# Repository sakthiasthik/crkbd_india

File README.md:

# Corne Indian ⌨️

A split mechanical keyboard **inspired by the original [CRKBD (Corne)](https://github.com/foostan/crkbd)** by [foostan](https://github.com/foostan). While the overall keyboard layout, key positions, and form factor follow the Corne design, the **entire schematic and PCB layout have been redesigned from scratch**.

The hardware has been engineered with a focus on the **Indian maker ecosystem**, using components that are readily available from Indian suppliers. The PCB has been designed to simplify manufacturing, assembly, troubleshooting, and long-term maintenance. If a component fails, it can be replaced easily without requiring hard-to-source imported parts — making the keyboard highly repairable and practical for everyday use.

---

## Highlights

- **Inspired by the CRKBD (Corne) split keyboard design**
- **Complete schematic designed from scratch**
- **Complete PCB layout designed from scratch**
- **Powered by RP2040** — affordable, powerful, and widely available in India (replaces the Pro Micro / ATmega32U4)
- **Hot-swappable switches** — no soldering required for switches
- Optimized for components that are **easily available from Indian suppliers**
- Designed for **easy manufacturing and assembly**
- Simplified **rework and repair** with accessible component placement
- **Fully open-source hardware** — anyone can build, modify, and maintain

---

## Design Files

All design files are in [`pcbs/corne-indian/`](pcbs/corne-indian/):

```
pcbs/corne-indian/corne-inidan-hotswap/
├── corne-inidan-hotswap.kicad_pro    # KiCad project
├── corne-inidan-hotswap.kicad_sch    # Main schematic
├── corne-inidan-hotswap.kicad_pcb    # PCB layout
├── left.kicad_sch                    # Left half schematic
├── right.kicad_sch                   # Right half schematic
├── corne-inidan-hotswap.step         # 3D model
└── corne_ibom.html                   # Interactive BOM
```

> Designed in **KiCad**. Open the `.kicad_pro` file to get started.

---

## Images

### Original CRKBD (Corne) — The Inspiration

### Corne Indian — Our Design

<!-- TODO: Add Corne Indian PCB render (top view) -->

<!-- TODO: Add Corne Indian PCB render (bottom view) -->

<!-- TODO: Add assembled Corne Indian keyboard photo -->

<!-- TODO: Add Corne Indian 3D render -->
<!-- [Corne Indian 3D Render](https://via.placeholder.com/800x600/0f3460/e0e0e0?text=Corne+Indian+-+3D+Render) -->

---

## Comparison: Original CRKBD vs Corne Indian

| Feature | Original CRKBD | Corne Indian |
|---|---|---|
| **Microcontroller** | Pro Micro (ATmega32U4) | RP2040 |
| **Switch mounting** | Soldered / Hotswap | Hot-swappable |
| **Component sourcing** | International | India-focused |
| **Schematic** | Original by foostan | Redesigned from scratch |
| **PCB Layout** | Original by foostan | Redesigned from scratch |
| **License** | MIT | MIT |

---

## Credits

This project stands on the shoulders of the excellent **[CRKBD (Corne)](https://github.com/foostan/crkbd)** by **foostan**. The Corne Indian retains the same split-keyboard layout and form factor that makes the Corne great, while re-engineering the hardware for the Indian maker community.

---

## License

This project is licensed under the **MIT License** — see [LICENSE](LICENSE) for details.

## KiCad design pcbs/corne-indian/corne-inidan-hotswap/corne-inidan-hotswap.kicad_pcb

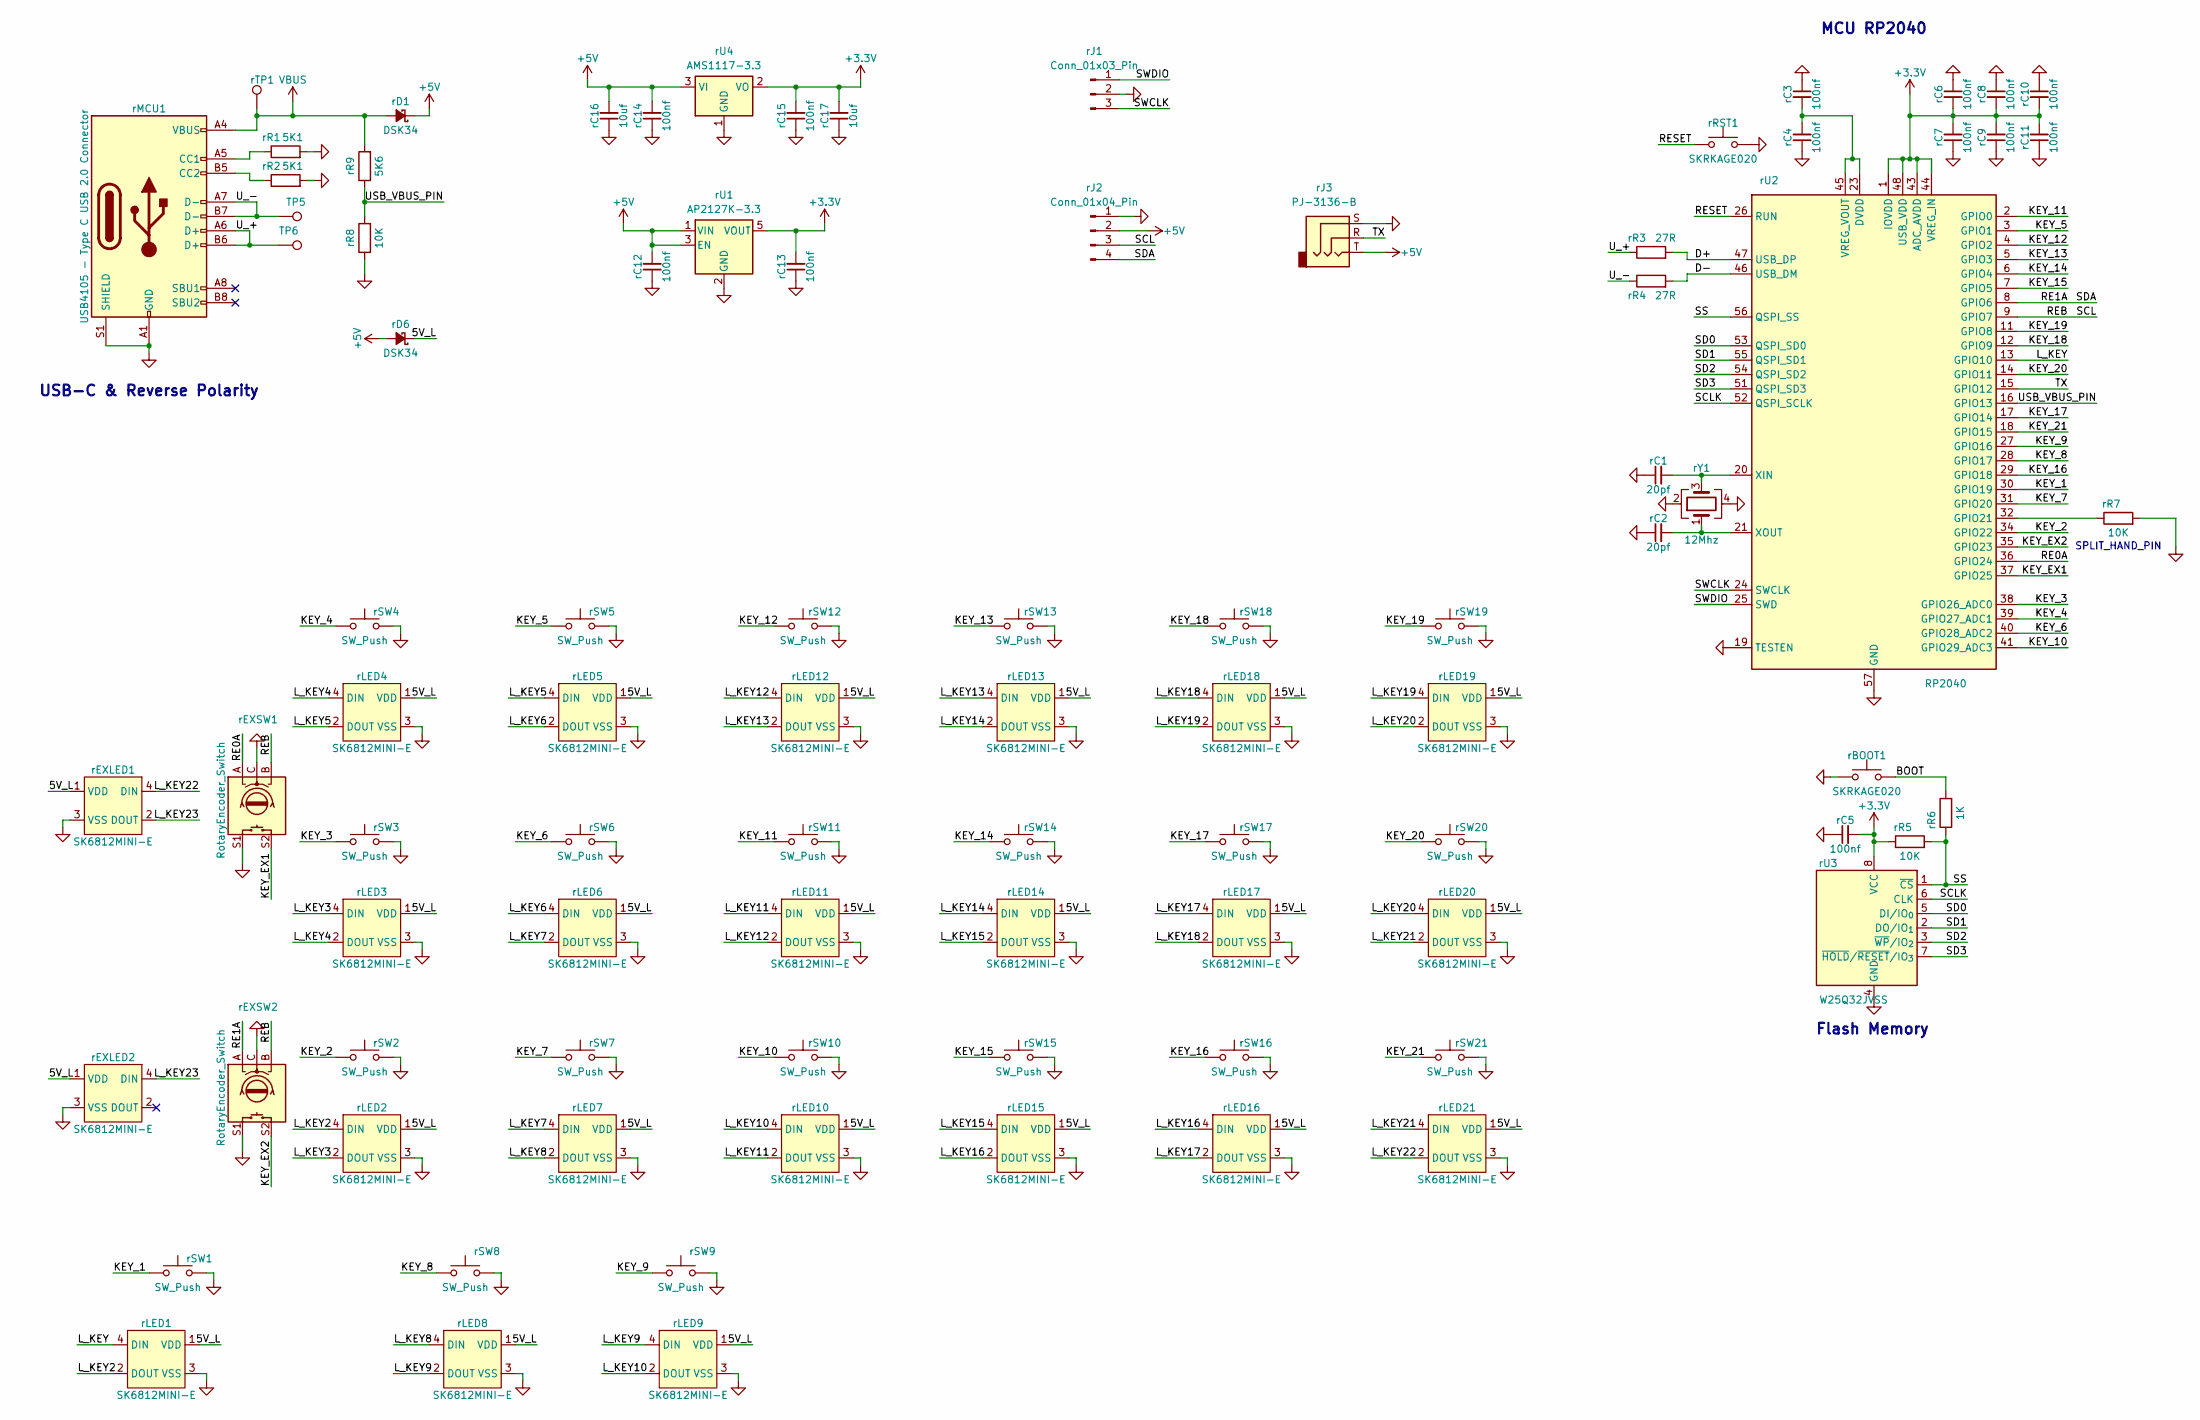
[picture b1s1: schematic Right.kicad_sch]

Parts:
TP5, TP6: TestPoint; TestPoint_Pad_D1.0mm
rBOOT1: SKRKAGE020; SW_Push_SPST_NO_Alps_SKRK; Manufacturer_Part_Number SKRKAGE020; LCSC_Part C18077675
rC1, rC2: 20pf; C_0603_1608Metric
rC3, rC4, rC5, rC6, rC7, rC8, rC9, rC10, rC11, rC12, rC13, rC14, rC15: 100nf; C_0603_1608Metric; Manufacturer_Part_Number MC0603B104K250CT; LCSC_Part C14663
rC16, rC17: 10uf; C_0603_1608Metric
rD1, rD6: DSK34; D_SOD-123F; Manufacturer_Part_Numbe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 DSK34; LCSC_Part C727076
rEXLED1, rEXLED2: SK6812MINI-E; YS-SK6812MINI-E
rEXSW1, rEXSW2: RotaryEncoder_Switch; keyswitch_cherrymx_hotswap_1u_rotary_encoder_ec12
rJ1: Conn_01x03_Pin; PinHeader_1x03_P2.54mm_Vertical
rJ2: Conn_01x04_Pin; PinHeader_1x04_P2.54mm_Vertical
rJ3: PJ-3136-B
rLED1, rLED2, rLED3, rLED4, rLED5, rLED6, rLED7, rLED8, rLED9, rLED10, rLED11, rLED12, rLED13, rLED14, rLED15, rLED16, rLED17, rLED18, rLED19, rLED20, rLED21: SK6812MINI-E; YS-SK6812MINI-E
rMCU1: USB4105 - Type C USB 2.0 Connector; USB_C_Receptacle_GCT_USB4105-xx-A_16P_TopMnt_Horizontal; Manufacturer_Part_Number USB4105-15-A-120; LCSC_Part C2988369
rR1, rR2: 5K1; R_0603_1608Metric; Manufacturer_Part_Number MCWR06X5101FTL; LCSC_Part C23186
rR3, rR4: 27R; R_0603_1608Metric
rR5, rR7, rR8: 10K; R_0603_1608Metric; Manufacturer_Part_Number MCWR06X1002FTL; LCSC_Part C25804
rR6: 1K; R_0603_1608Metric
rR9: 5K6; R_0603_1608Metric
rRST1: SKRKAGE020; SW_Push_SPST_NO_Alps_SKRK; Manufacturer_Part_Number SKRKAGE020; LCSC_Part C18077675
rSW1: SW_Push; SW_Cherry_MX_1.50u_Hotswap
rSW2, rSW3, rSW4, rSW5, rSW6, rSW7, rSW8, rSW9, rSW10, rSW11, rSW12, rSW13, rSW14, rSW15, rSW16, rSW17, rSW18, rSW19, rSW20, rSW21: SW_Push; SW_Cherry_MX_1.00u_Hotswap
rTP1: TestPoint; TestPoint_Pad_D1.0mm
rU1: AP2127K-3.3; SOT-23-5
rU2: RP2040; QFN-56-1EP_7x7mm_P0.4mm_EP3.2x3.2mm; Manufacturer_Part_Number RP2040; LCSC_Part C2040
rU3: W25Q32JVSS; SOIC-8_5.3x5.3mm_P1.27mm; Manufacturer_Part_Number W25Q32JVSSIQ; LCSC_Part C98163
rU4: AMS1117-3.3; SOT-223-3_TabPin2
rY1: 12Mhz; Crystal_SMD_Abracon_ABM8AIG-4Pin_3.2x2.5mm

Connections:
+3.3V: rC5.2, rC6.2, rC7.2, rC8.2, rC9.2, rC10.2, rC11.2, rC13.2, rC15.2, rC17.2, rR5.1, rU1.5 (VOUT), rU2.1 (IOVDD), rU2.10 (IOVDD), rU2.22 (IOVDD), rU2.33 (IOVDD), rU2.42 (IOVDD), rU2.43 (ADC_AVDD), rU2.44 (VREG_IN), rU2.48 (USB_VDD), rU2.49 (IOVDD), rU3.8 (VCC), rU4.2 (VO); also elsewhere on the board
+5V: rC12.2, rC14.2, rC16.2, rD1.1 (K), rD6.2 (A), rJ2.2, rJ3.T, rU1.1 (VIN), rU1.3 (EN), rU4.3 (VI); also elsewhere on the board
/Right/5V_L: rD6.1 (K), rEXLED1.1 (VDD), rEXLED2.1 (VDD), rLED1.1 (VDD), rLED2.1 (VDD), rLED3.1 (VDD), rLED4.1 (VDD), rLED5.1 (VDD), rLED6.1 (VDD), rLED7.1 (VDD), rLED8.1 (VDD), rLED9.1 (VDD), rLED10.1 (VDD), rLED11.1 (VDD), rLED12.1 (VDD), rLED13.1 (VDD), rLED14.1 (VDD), rLED15.1 (VDD), rLED16.1 (VDD), rLED17.1 (VDD), rLED18.1 (VDD), rLED19.1 (VDD), rLED20.1 (VDD), rLED21.1 (VDD)
/Right/BOOT: rBOOT1.1, rR6.2
/Right/D+: rR3.2, rU2.47 (USB_DP)
/Right/D-: rR4.2, rU2.46 (USB_DM)
/Right/KEY_1: rSW1.1, rU2.30 (GPIO19)
/Right/KEY_2: rSW2.1, rU2.34 (GPIO22)
/Right/KEY_3: rSW3.1, rU2.38 (GPIO26_ADC0)
/Right/KEY_4: rSW4.1, rU2.39 (GPIO27_ADC1)
/Right/KEY_5: rSW5.1, rU2.3 (GPIO1)
/Right/KEY_6: rSW6.1, rU2.40 (GPIO28_ADC2)
/Right/KEY_7: rSW7.1, rU2.31 (GPIO20)
/Right/KEY_8: rSW8.1, rU2.28 (GPIO17)
/Right/KEY_9: rSW9.1, rU2.27 (GPIO16)
/Right/KEY_10: rSW10.1, rU2.41 (GPIO29_ADC3)
/Right/KEY_11: rSW11.1, rU2.2 (GPIO0)
/Right/KEY_12: rSW12.1, rU2.4 (GPIO2)
/Right/KEY_13: rSW13.1, rU2.5 (GPIO3)
/Right/KEY_14: rSW14.1, rU2.6 (GPIO4)
/Right/KEY_15: rSW15.1, rU2.7 (GPIO5)
/Right/KEY_16: rSW16.1, rU2.29 (GPIO18)
/Right/KEY_17: rSW17.1, rU2.17 (GPIO14)
/Right/KEY_18: rSW18.1, rU2.12 (GPIO9)
/Right/KEY_19: rSW19.1, rU2.11 (GPIO8)
/Right/KEY_20: rSW20.1, rU2.14 (GPIO11)
/Right/KEY_21: rSW21.1, rU2.18 (GPIO15)
/Right/KEY_EX1: rEXSW1.S2, rU2.37 (GPIO25)
/Right/KEY_EX2: rEXSW2.S2, rU2.35 (GPIO23)
/Right/L_KEY: rLED1.4 (DIN), rU2.13 (GPIO10)
/Right/L_KEY2: rLED1.2 (DOUT), rLED2.4 (DIN)
/Right/L_KEY3: rLED2.2 (DOUT), rLED3.4 (DIN)
/Right/L_KEY4: rLED3.2 (DOUT), rLED4.4 (DIN)
/Right/L_KEY5: rLED4.2 (DOUT), rLED5.4 (DIN)
/Right/L_KEY6: rLED5.2 (DOUT), rLED6.4 (DIN)
/Right/L_KEY7: rLED6.2 (DOUT), rLED7.4 (DIN)
/Right/L_KEY8: rLED7.2 (DOUT), rLED8.4 (DIN)
/Right/L_KEY9: rLED8.2 (DOUT), rLED9.4 (DIN)
/Right/L_KEY10: rLED9.2 (DOUT), rLED10.4 (DIN)
/Right/L_KEY11: rLED10.2 (DOUT), rLED11.4 (DIN)
/Right/L_KEY12: rLED11.2 (DOUT), rLED12.4 (DIN)
/Right/L_KEY13: rLED12.2 (DOUT), rLED13.4 (DIN)
/Right/L_KEY14: rLED13.2 (DOUT), rLED14.4 (DIN)
/Right/L_KEY15: rLED14.2 (DOUT), rLED15.4 (DIN)
/Right/L_KEY16: rLED15.2 (DOUT), rLED16.4 (DIN)
/Right/L_KEY17: rLED16.2 (DOUT), rLED17.4 (DIN)
/Right/L_KEY18: rLED17.2 (DOUT), rLED18.4 (DIN)
/Right/L_KEY19: rLED18.2 (DOUT), rLED19.4 (DIN)
/Right/L_KEY20: rLED19.2 (DOUT), rLED20.4 (DIN)
/Right/L_KEY21: rLED20.2 (DOUT), rLED21.4 (DIN)
/Right/L_KEY22: rEXLED1.4 (DIN), rLED21.2 (DOUT)
/Right/L_KEY23: rEXLED1.2 (DOUT), rEXLED2.4 (DIN)
/Right/RE0A: rEXSW1.A, rU2.36 (GPIO24)
/Right/RE1A: rEXSW2.A, rJ2.4, rU2.8 (GPIO6)
/Right/REB: rEXSW1.B, rEXSW2.B, rJ2.3, rU2.9 (GPIO7)
/Right/RESET: rRST1.1, rU2.26 (RUN)
/Right/SCLK: rU2.52 (QSPI_SCLK), rU3.6 (CLK)
/Right/SD0: rU2.53 (QSPI_SD0), rU3.5 (DI/IO_{0})
/Right/SD1: rU2.55 (QSPI_SD1), rU3.2 (DO/IO_{1})
/Right/SD2: rU2.54 (QSPI_SD2), rU3.3 (~WP/IO_{2})
/Right/SD3: rU2.51 (QSPI_SD3), rU3.7 (~HOLD/~RESET/IO_{3})
/Right/SS: rR5.2, rR6.1, rU2.56 (QSPI_SS), rU3.1 (~CS)
/Right/SWCLK: rJ1.3, rU2.24 (SWCLK)
/Right/SWDIO: rJ1.1, rU2.25 (SWD)
/Right/TX: rJ3.R, rU2.15 (GPIO12)
/Right/USB_VBUS_PIN: rR8.2, rR9.1, rU2.16 (GPIO13)
/Right/U_+: TP6.1, rMCU1.A6 (D+), rMCU1.B6 (D+), rR3.1
/Right/U_-: TP5.1, rMCU1.A7 (D-), rMCU1.B7 (D-), rR4.1
GND: rBOOT1.2, rC1.1, rC2.1, rC3.1, rC4.1, rC5.1, rC6.1, rC7.1, rC8.1, rC9.1, rC10.1, rC11.1, rC12.1, rC13.1, rC14.1, rC15.1, rC16.1, rC17.1, rEXLED1.3 (VSS), rEXLED2.3 (VSS), rEXSW1.C, rEXSW1.S1, rEXSW2.C, rEXSW2.S1, rJ1.2, rJ2.1, rJ3.S, rLED1.3 (VSS), rLED2.3 (VSS), rLED3.3 (VSS), rLED4.3 (VSS), rLED5.3 (VSS), rLED6.3 (VSS), rLED7.3 (VSS), rLED8.3 (VSS), rLED9.3 (VSS), rLED10.3 (VSS), rLED11.3 (VSS), rLED12.3 (VSS), rLED13.3 (VSS), rLED14.3 (VSS), rLED15.3 (VSS), rLED16.3 (VSS), rLED17.3 (VSS), rLED18.3 (VSS), rLED19.3 (VSS), rLED20.3 (VSS), rLED21.3 (VSS), rMCU1.A1 (GND), rMCU1.A12 (GND), rMCU1.B1 (GND), rMCU1.B12 (GND), rMCU1.S1 (SHIELD), rR1.2, rR2.2, rR7.2, rR8.1, rRST1.2, rSW1.2, rSW2.2, rSW3.2, rSW4.2, rSW5.2, rSW6.2, rSW7.2, rSW8.2, rSW9.2, rSW10.2, rSW11.2, rSW12.2, rSW13.2, rSW14.2, rSW15.2, rSW16.2, rSW17.2, rSW18.2, rSW19.2, rSW20.2, rSW21.2, rU1.2 (GND), rU2.19 (TESTEN), rU2.57 (GND), rU3.4 (GND), rU4.1 (GND), rY1.2, rY1.4; also elsewhere on the board
unnamed: rMCU1.A5 (CC1), rR1.1
unnamed: rMCU1.B5 (CC2), rR2.1
unnamed: rR7.1, rU2.32 (GPIO21)
unnamed: rC3.2, rC4.2, rU2.23 (DVDD), rU2.45 (VREG_VOUT), rU2.50 (DVDD)
unnamed: rC1.2, rU2.20 (XIN), rY1.3
unnamed: rC2.2, rU2.21 (XOUT), rY1.1
VBUS: rD1.2 (A), rMCU1.A4 (VBUS), rMCU1.A9 (VBUS), rMCU1.B4 (VBUS), rMCU1.B9 (VBUS), rR9.2, rTP1.1; also elsewhere on the board

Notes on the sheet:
MCU RP2040
Flash Memory
SPLIT_HAND_PIN
USB-C & Reverse Polarity

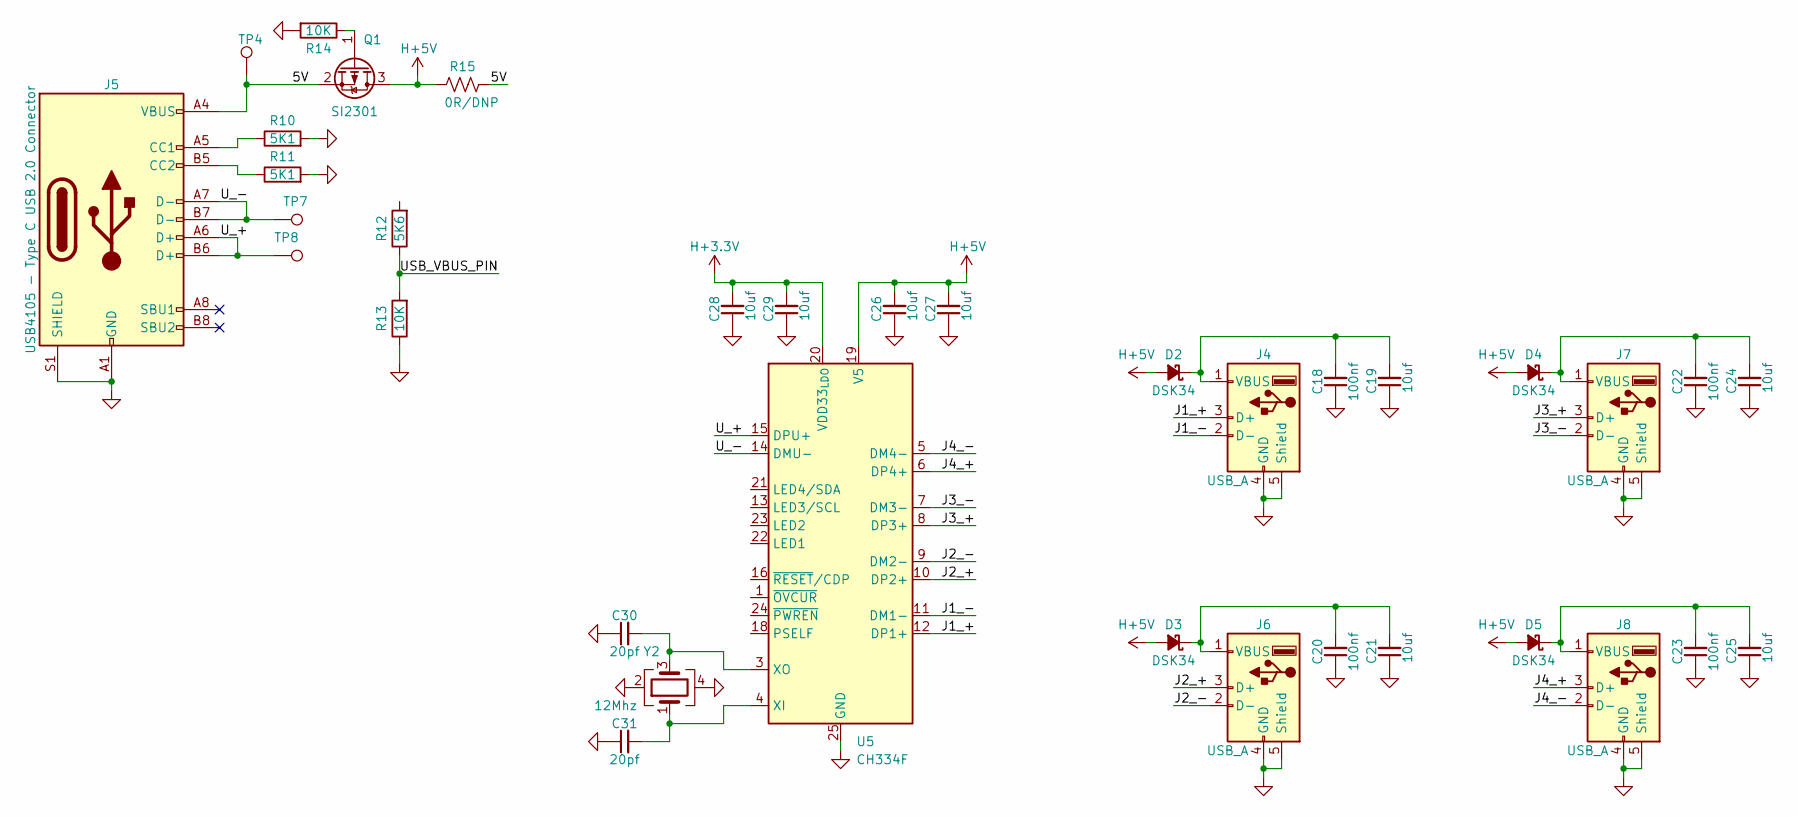
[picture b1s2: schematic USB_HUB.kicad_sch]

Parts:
C18, C20, C22, C23: 100nf; C_0603_1608Metric; Manufacturer_Part_Number MC0603B104K250CT; LCSC_Part C14663
C19, C21, C24, C25, C26, C27, C28, C29: 10uf; C_0805_2012Metric; Manufacturer_Part_Number CL21A106KAYNNNG; LCSC_Part C15850
C30, C31: 20pf; C_0603_1608Metric
D2, D3, D4, D5: DSK34; D_SOD-123F; Manufacturer_Part_Numbe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 DSK34; LCSC_Part C727076
J4, J6, J7, J8: USB_A; USB_A_Molex_67643_Horizontal
J5: USB4105 - Type C USB 2.0 Connector; USB_C_Receptacle_GCT_USB4105-xx-A_16P_TopMnt_Horizontal; Manufacturer_Part_Number USB4105-15-A-120; LCSC_Part C2988369
Q1: SI2301; SOT-23; Manufacturer_Part_Number SI2301; LCSC_Part C382312
R10, R11: 5K1; R_0603_1608Metric; Manufacturer_Part_Number MCWR06X5101FTL; LCSC_Part C23186
R12: 5K6; R_0603_1608Metric
R13, R14: 10K; R_0603_1608Metric; Manufacturer_Part_Number MCWR06X1002FTL; LCSC_Part C25804
R15: 0R/DNP; R_0603_1608Metric; Manufacturer_Part_Number MCWR06X000 PTL; LCSC_Part C21189
TP4, TP7, TP8: TestPoint; TestPoint_Pad_D1.0mm
U5: CH334F; QFN-24-1EP_4x4mm_P0.5mm_EP2.7x2.7mm
Y2: 12Mhz; Crystal_SMD_Abracon_ABM8AIG-4Pin_3.2x2.5mm

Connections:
/USB_HUB/5V: J5.A4 (VBUS), J5.A9 (VBUS), J5.B4 (VBUS), J5.B9 (VBUS), Q1.2 (S), R15.2, TP4.1
/USB_HUB/J1_+: J4.3 (D+), U5.12 (DP1+)
/USB_HUB/J1_-: J4.2 (D-), U5.11 (DM1-)
/USB_HUB/J2_+: J6.3 (D+), U5.10 (DP2+)
/USB_HUB/J2_-: J6.2 (D-), U5.9 (DM2-)
/USB_HUB/J3_+: J7.3 (D+), U5.8 (DP3+)
/USB_HUB/J3_-: J7.2 (D-), U5.7 (DM3-)
/USB_HUB/J4_+: J8.3 (D+), U5.6 (DP4+)
/USB_HUB/J4_-: J8.2 (D-), U5.5 (DM4-)
/USB_HUB/USB_VBUS_PIN: R12.1, R13.2
/USB_HUB/U_+: J5.A6 (D+), J5.B6 (D+), TP8.1, U5.15 (DPU+)
/USB_HUB/U_-: J5.A7 (D-), J5.B7 (D-), TP7.1, U5.14 (DMU-)
GND: C18.1, C19.1, C20.1, C21.1, C22.1, C23.1, C24.1, C25.1, C26.1, C27.1, C28.1, C29.1, C30.1, C31.1, J4.4 (GND), J4.5 (Shield), J5.A1 (GND), J5.A12 (GND), J5.B1 (GND), J5.B12 (GND), J5.S1 (SHIELD), J6.4 (GND), J6.5 (Shield), J7.4 (GND), J7.5 (Shield), J8.4 (GND), J8.5 (Shield), R10.2, R11.2, R13.1, R14.2, U5.25 (GND), Y2.2, Y2.4; also elsewhere on the board
H+3.3V: C28.2, C29.2, U5.20 (VDD33_{LDO})
H+5V: C26.2, C27.2, D2.2 (A), D3.2 (A), D4.2 (A), D5.2 (A), Q1.3 (D), R15.1, U5.19 (V5)
unnamed: C18.2, C19.2, D2.1 (K), J4.1 (VBUS)
unnamed: C20.2, C21.2, D3.1 (K), J6.1 (VBUS)
unnamed: C22.2, C24.2, D4.1 (K), J7.1 (VBUS)
unnamed: C23.2, C25.2, D5.1 (K), J8.1 (VBUS)
unnamed: J5.A5 (CC1), R10.1
unnamed: J5.B5 (CC2), R11.1
unnamed: Q1.1 (G), R14.1
unnamed: C31.2, U5.4 (XI), Y2.1
unnamed: C30.2, U5.3 (XO), Y2.3

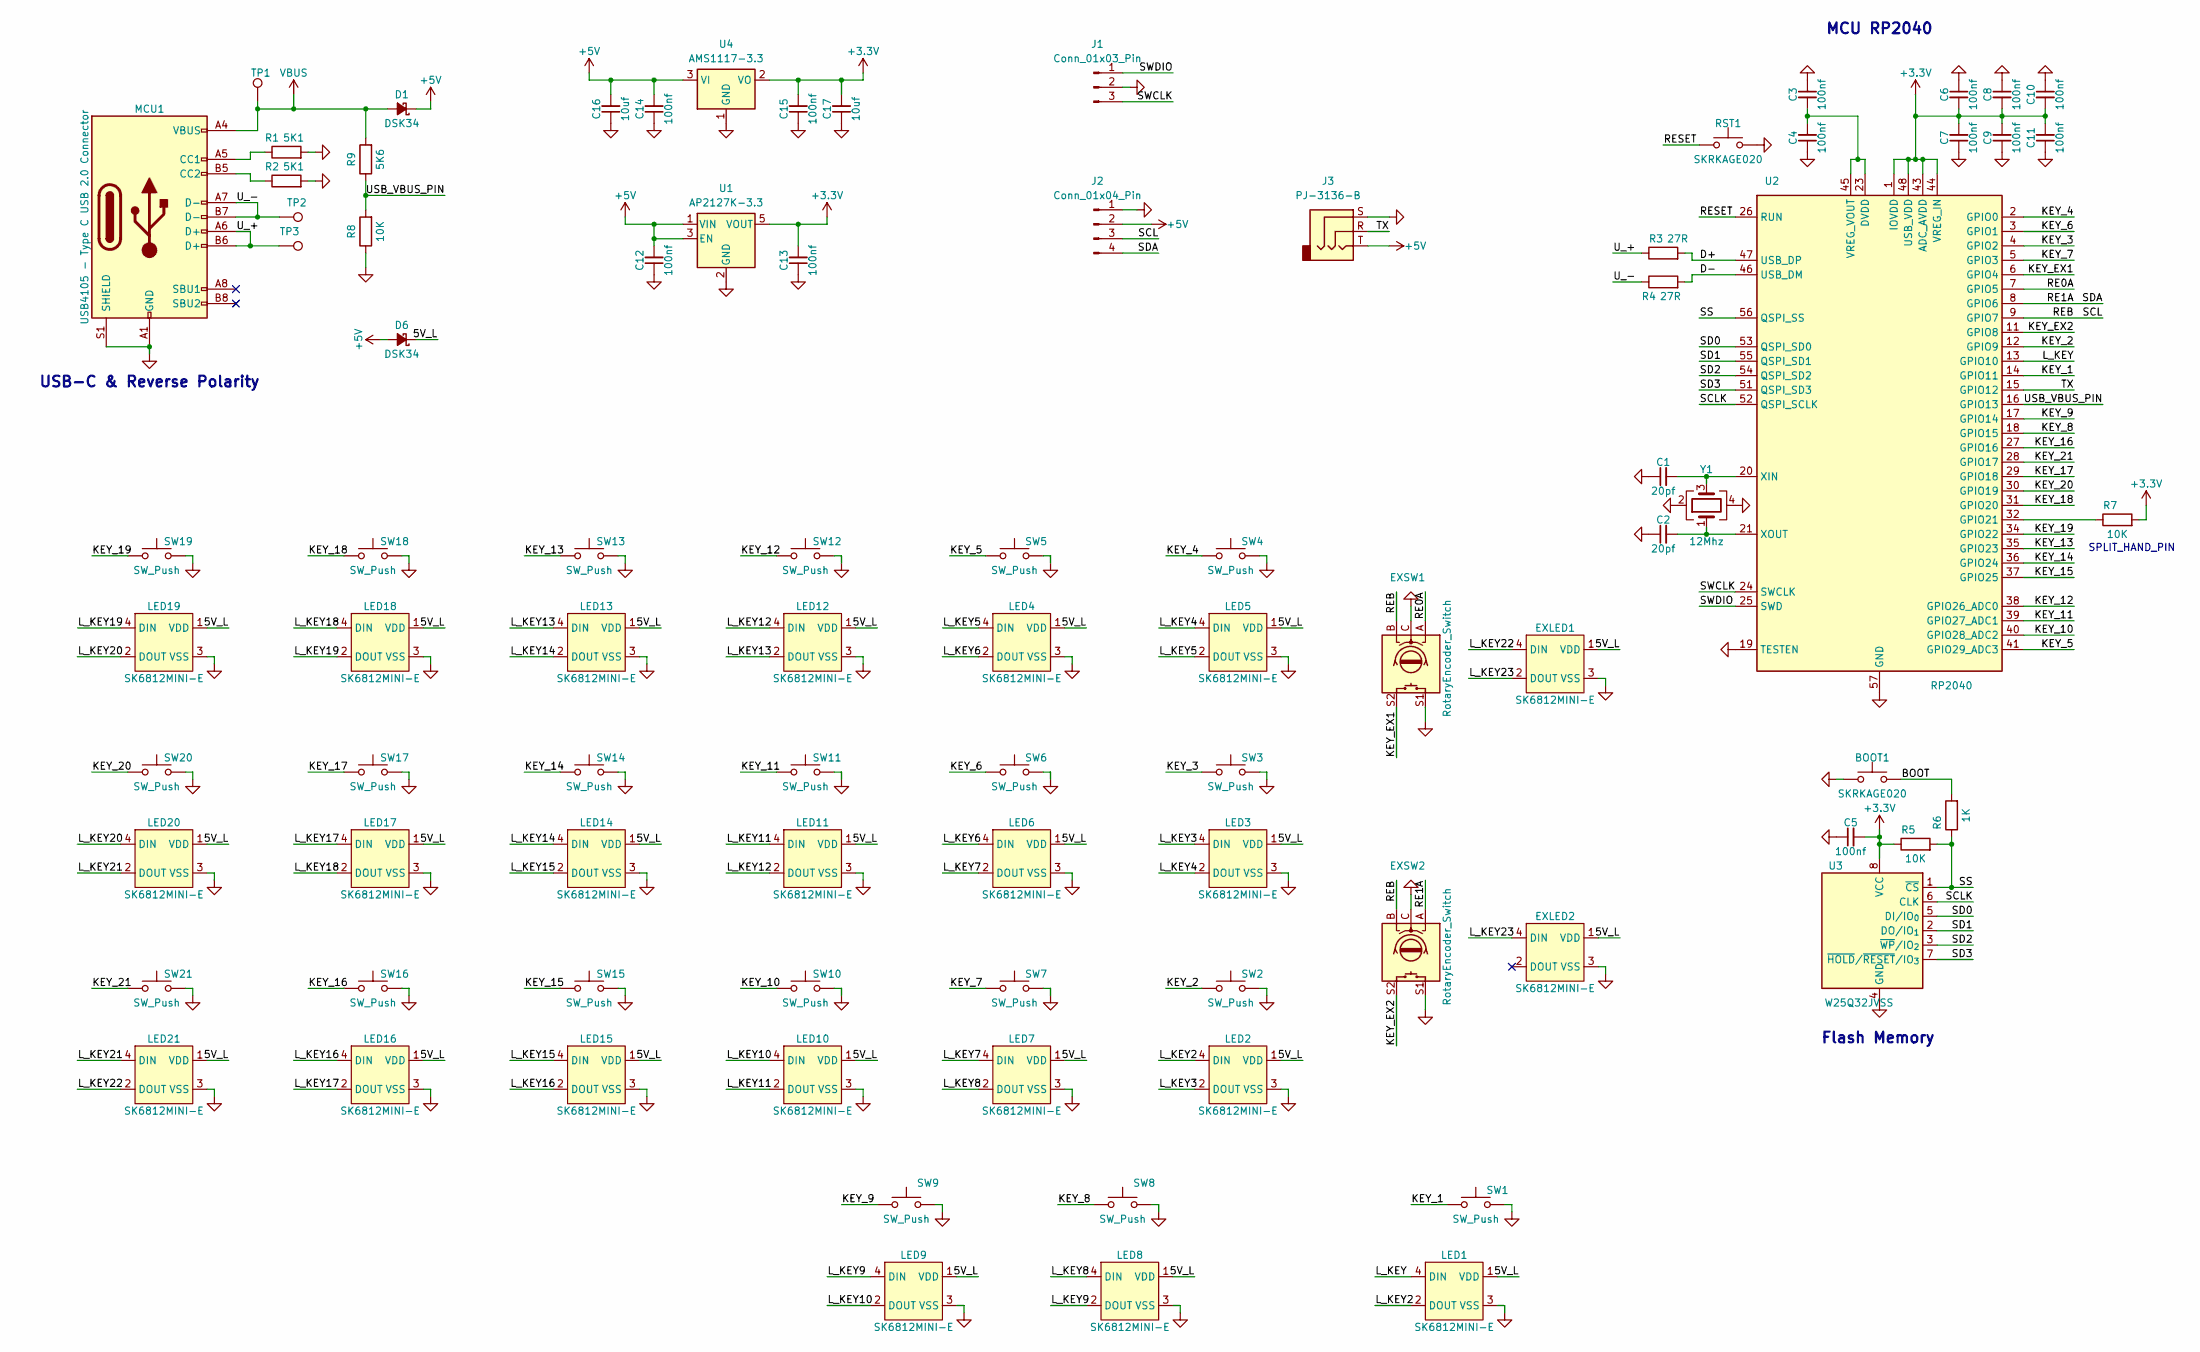
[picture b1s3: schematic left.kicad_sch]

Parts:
BOOT1: SKRKAGE020; SW_Push_SPST_NO_Alps_SKRK; Manufacturer_Part_Number SKRKAGE020; LCSC_Part C18077675
C1, C2: 20pf; C_0603_1608Metric
C3, C4, C5, C6, C7, C8, C9, C10, C11, C12, C13, C14, C15: 100nf; C_0603_1608Metric; Manufacturer_Part_Number MC0603B104K250CT; LCSC_Part C14663
C16, C17: 10uf; C_0603_1608Metric
D1, D6: DSK34; D_SOD-123F; Manufacturer_Part_Numbe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 DSK34; LCSC_Part C727076
EXLED1, EXLED2: SK6812MINI-E; YS-SK6812MINI-E
EXSW1, EXSW2: RotaryEncoder_Switch; keyswitch_cherrymx_hotswap_1u_rotary_encoder_ec12
J1: Conn_01x03_Pin; PinHeader_1x03_P2.54mm_Vertical
J2: Conn_01x04_Pin; PinHeader_1x04_P2.54mm_Vertical
J3: PJ-3136-B
LED1, LED2, LED3, LED4, LED5, LED6, LED7, LED8, LED9, LED10, LED11, LED12, LED13, LED14, LED15, LED16, LED17, LED18, LED19, LED20, LED21: SK6812MINI-E; YS-SK6812MINI-E
MCU1: USB4105 - Type C USB 2.0 Connector; USB_C_Receptacle_GCT_USB4105-xx-A_16P_TopMnt_Horizontal; Manufacturer_Part_Number USB4105-15-A-120; LCSC_Part C2988369
R1, R2: 5K1; R_0603_1608Metric; Manufacturer_Part_Number MCWR06X5101FTL; LCSC_Part C23186
R3, R4: 27R; R_0603_1608Metric
R5, R7, R8: 10K; R_0603_1608Metric; Manufacturer_Part_Number MCWR06X1002FTL; LCSC_Part C25804
R6: 1K; R_0603_1608Metric
R9: 5K6; R_0603_1608Metric
RST1: SKRKAGE020; SW_Push_SPST_NO_Alps_SKRK; Manufacturer_Part_Number SKRKAGE020; LCSC_Part C18077675
SW1: SW_Push; SW_Cherry_MX_1.50u_Hotswap
SW2, SW3, SW4, SW5, SW6, SW7, SW8, SW9, SW10, SW11, SW12, SW13, SW14, SW15, SW16, SW17, SW18, SW19, SW20, SW21: SW_Push; SW_Cherry_MX_1.00u_Hotswap
TP1, TP2, TP3: TestPoint; TestPoint_Pad_D1.0mm
U1: AP2127K-3.3; SOT-23-5
U2: RP2040; QFN-56-1EP_7x7mm_P0.4mm_EP3.2x3.2mm; Manufacturer_Part_Number RP2040; LCSC_Part C2040
U3: W25Q32JVSS; SOIC-8_5.3x5.3mm_P1.27mm; Manufacturer_Part_Number W25Q32JVSSIQ; LCSC_Part C98163
U4: AMS1117-3.3; SOT-223-3_TabPin2
Y1: 12Mhz; Crystal_SMD_Abracon_ABM8AIG-4Pin_3.2x2.5mm

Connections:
+3.3V: C5.2, C6.2, C7.2, C8.2, C9.2, C10.2, C11.2, C13.2, C15.2, C17.2, R5.1, R7.2, U1.5 (VOUT), U2.1 (IOVDD), U2.10 (IOVDD), U2.22 (IOVDD), U2.33 (IOVDD), U2.42 (IOVDD), U2.43 (ADC_AVDD), U2.44 (VREG_IN), U2.48 (USB_VDD), U2.49 (IOVDD), U3.8 (VCC), U4.2 (VO); also elsewhere on the board
+5V: C12.2, C14.2, C16.2, D1.1 (K), D6.2 (A), J2.2, J3.T, U1.1 (VIN), U1.3 (EN), U4.3 (VI); also elsewhere on the board
/left/5V_L: D6.1 (K), EXLED1.1 (VDD), EXLED2.1 (VDD), LED1.1 (VDD), LED2.1 (VDD), LED3.1 (VDD), LED4.1 (VDD), LED5.1 (VDD), LED6.1 (VDD), LED7.1 (VDD), LED8.1 (VDD), LED9.1 (VDD), LED10.1 (VDD), LED11.1 (VDD), LED12.1 (VDD), LED13.1 (VDD), LED14.1 (VDD), LED15.1 (VDD), LED16.1 (VDD), LED17.1 (VDD), LED18.1 (VDD), LED19.1 (VDD), LED20.1 (VDD), LED21.1 (VDD)
/left/BOOT: BOOT1.1, R6.2
/left/D+: R3.2, U2.47 (USB_DP)
/left/D-: R4.2, U2.46 (USB_DM)
/left/KEY_1: SW1.1, U2.14 (GPIO11)
/left/KEY_2: SW2.1, U2.12 (GPIO9)
/left/KEY_3: SW3.1, U2.4 (GPIO2)
/left/KEY_4: SW4.1, U2.2 (GPIO0)
/left/KEY_5: SW5.1, U2.41 (GPIO29_ADC3)
/left/KEY_6: SW6.1, U2.3 (GPIO1)
/left/KEY_7: SW7.1, U2.5 (GPIO3)
/left/KEY_8: SW8.1, U2.18 (GPIO15)
/left/KEY_9: SW9.1, U2.17 (GPIO14)
/left/KEY_10: SW10.1, U2.40 (GPIO28_ADC2)
/left/KEY_11: SW11.1, U2.39 (GPIO27_ADC1)
/left/KEY_12: SW12.1, U2.38 (GPIO26_ADC0)
/left/KEY_13: SW13.1, U2.35 (GPIO23)
/left/KEY_14: SW14.1, U2.36 (GPIO24)
/left/KEY_15: SW15.1, U2.37 (GPIO25)
/left/KEY_16: SW16.1, U2.27 (GPIO16)
/left/KEY_17: SW17.1, U2.29 (GPIO18)
/left/KEY_18: SW18.1, U2.31 (GPIO20)
/left/KEY_19: SW19.1, U2.34 (GPIO22)
/left/KEY_20: SW20.1, U2.30 (GPIO19)
/left/KEY_21: SW21.1, U2.28 (GPIO17)
/left/KEY_EX1: EXSW1.S2, U2.6 (GPIO4)
/left/KEY_EX2: EXSW2.S2, U2.11 (GPIO8)
/left/L_KEY: LED1.4 (DIN), U2.13 (GPIO10)
/left/L_KEY2: LED1.2 (DOUT), LED2.4 (DIN)
/left/L_KEY3: LED2.2 (DOUT), LED3.4 (DIN)
/left/L_KEY4: LED3.2 (DOUT), LED5.4 (DIN)
/left/L_KEY5: LED4.4 (DIN), LED5.2 (DOUT)
/left/L_KEY6: LED4.2 (DOUT), LED6.4 (DIN)
/left/L_KEY7: LED6.2 (DOUT), LED7.4 (DIN)
/left/L_KEY8: LED7.2 (DOUT), LED8.4 (DIN)
/left/L_KEY9: LED8.2 (DOUT), LED9.4 (DIN)
/left/L_KEY10: LED9.2 (DOUT), LED10.4 (DIN)
/left/L_KEY11: LED10.2 (DOUT), LED11.4 (DIN)
/left/L_KEY12: LED11.2 (DOUT), LED12.4 (DIN)
/left/L_KEY13: LED12.2 (DOUT), LED13.4 (DIN)
/left/L_KEY14: LED13.2 (DOUT), LED14.4 (DIN)
/left/L_KEY15: LED14.2 (DOUT), LED15.4 (DIN)
/left/L_KEY16: LED15.2 (DOUT), LED16.4 (DIN)
/left/L_KEY17: LED16.2 (DOUT), LED17.4 (DIN)
/left/L_KEY18: LED17.2 (DOUT), LED18.4 (DIN)
/left/L_KEY19: LED18.2 (DOUT), LED19.4 (DIN)
/left/L_KEY20: LED19.2 (DOUT), LED20.4 (DIN)
/left/L_KEY21: LED20.2 (DOUT), LED21.4 (DIN)
/left/L_KEY22: EXLED1.4 (DIN), LED21.2 (DOUT)
/left/L_KEY23: EXLED1.2 (DOUT), EXLED2.4 (DIN)
/left/RE0A: EXSW1.A, U2.7 (GPIO5)
/left/RE1A: EXSW2.A, J2.4, U2.8 (GPIO6)
/left/REB: EXSW1.B, EXSW2.B, J2.3, U2.9 (GPIO7)
/left/RESET: RST1.1, U2.26 (RUN)
/left/SCLK: U2.52 (QSPI_SCLK), U3.6 (CLK)
/left/SD0: U2.53 (QSPI_SD0), U3.5 (DI/IO_{0})
/left/SD1: U2.55 (QSPI_SD1), U3.2 (DO/IO_{1})
/left/SD2: U2.54 (QSPI_SD2), U3.3 (~WP/IO_{2})
/left/SD3: U2.51 (QSPI_SD3), U3.7 (~HOLD/~RESET/IO_{3})
/left/SS: R5.2, R6.1, U2.56 (QSPI_SS), U3.1 (~CS)
/left/SWCLK: J1.3, U2.24 (SWCLK)
/left/SWDIO: J1.1, U2.25 (SWD)
/left/TX: J3.R, U2.15 (GPIO12)
/left/USB_VBUS_PIN: R8.2, R9.1, U2.16 (GPIO13)
/left/U_+: MCU1.A6 (D+), MCU1.B6 (D+), R3.1, TP3.1
/left/U_-: MCU1.A7 (D-), MCU1.B7 (D-), R4.1, TP2.1
GND: BOOT1.2, C1.1, C2.1, C3.1, C4.1, C5.1, C6.1, C7.1, C8.1, C9.1, C10.1, C11.1, C12.1, C13.1, C14.1, C15.1, C16.1, C17.1, EXLED1.3 (VSS), EXLED2.3 (VSS), EXSW1.C, EXSW1.S1, EXSW2.C, EXSW2.S1, J1.2, J2.1, J3.S, LED1.3 (VSS), LED2.3 (VSS), LED3.3 (VSS), LED4.3 (VSS), LED5.3 (VSS), LED6.3 (VSS), LED7.3 (VSS), LED8.3 (VSS), LED9.3 (VSS), LED10.3 (VSS), LED11.3 (VSS), LED12.3 (VSS), LED13.3 (VSS), LED14.3 (VSS), LED15.3 (VSS), LED16.3 (VSS), LED17.3 (VSS), LED18.3 (VSS), LED19.3 (VSS), LED20.3 (VSS), LED21.3 (VSS), MCU1.A1 (GND), MCU1.A12 (GND), MCU1.B1 (GND), MCU1.B12 (GND), MCU1.S1 (SHIELD), R1.2, R2.2, R8.1, RST1.2, SW1.2, SW2.2, SW3.2, SW4.2, SW5.2, SW6.2, SW7.2, SW8.2, SW9.2, SW10.2, SW11.2, SW12.2, SW13.2, SW14.2, SW15.2, SW16.2, SW17.2, SW18.2, SW19.2, SW20.2, SW21.2, U1.2 (GND), U2.19 (TESTEN), U2.57 (GND), U3.4 (GND), U4.1 (GND), Y1.2, Y1.4; also elsewhere on the board
unnamed: MCU1.A5 (CC1), R1.1
unnamed: MCU1.B5 (CC2), R2.1
unnamed: R7.1, U2.32 (GPIO21)
unnamed: C3.2, C4.2, U2.23 (DVDD), U2.45 (VREG_VOUT), U2.50 (DVDD)
unnamed: C1.2, U2.20 (XIN), Y1.3
unnamed: C2.2, U2.21 (XOUT), Y1.1
VBUS: D1.2 (A), MCU1.A4 (VBUS), MCU1.A9 (VBUS), MCU1.B4 (VBUS), MCU1.B9 (VBUS), R9.2, TP1.1; also elsewhere on the board

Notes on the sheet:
MCU RP2040
SPLIT_HAND_PIN
Flash Memory
USB-C & Reverse Polarity

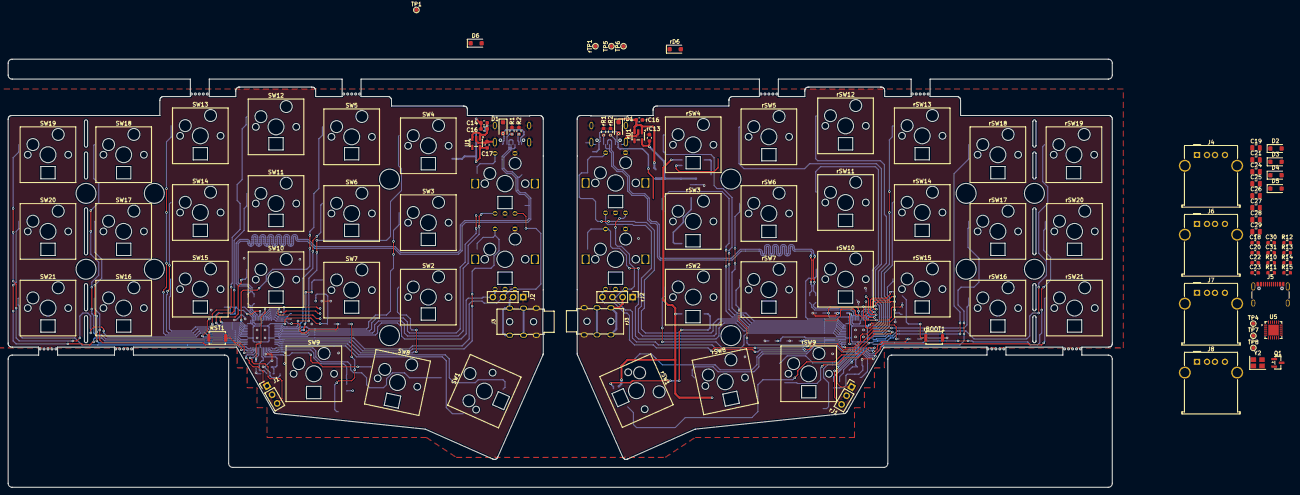
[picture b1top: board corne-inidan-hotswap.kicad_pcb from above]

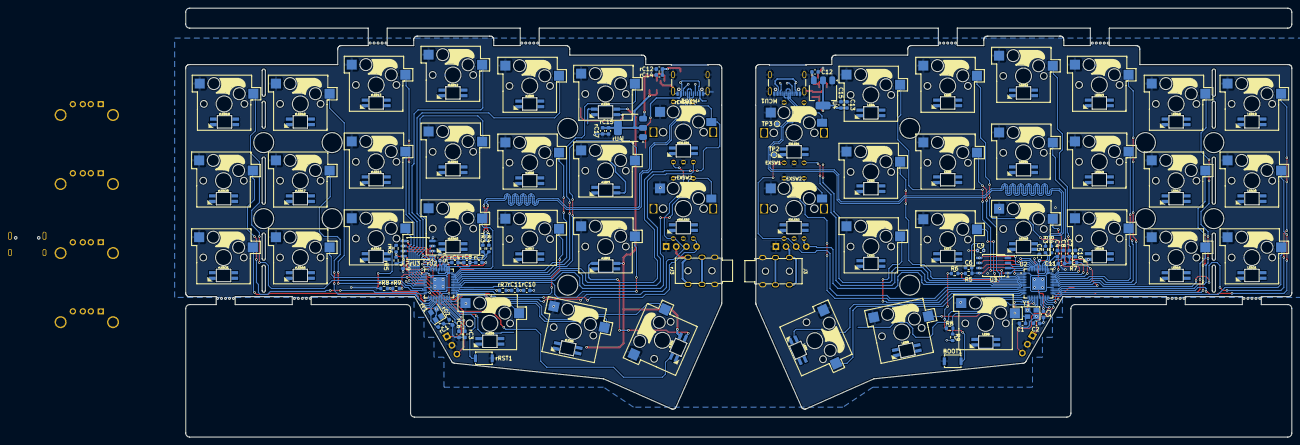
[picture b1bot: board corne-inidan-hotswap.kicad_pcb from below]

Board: 2 copper layers, 277.2 x 107.5 mm, 211 parts (107 on the bottom side), 171 nets.

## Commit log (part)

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2026-04-16 Need to change the Layout & design Based oin indian components availability
2026-04-16 Planning to change the Layout & Key based on components avilability on the India
2026-04-16 Left side LED & switch schematic added But need to check
2026-04-16 Schematic is Done for Right side But Only switch & LED & placement
2026-04-17 Rp2040 added to the shematic need to map to all Key Switch pins
2026-04-17 Mid of the renumbering & renaming
2026-04-19 Mid of the Placement still Rotary encoder is not done
2026-04-20 Mid of the Component placement still the Rotarty nob is not done
2026-04-20 Rotart encode also added in PCB layout
2026-04-22 Mid of the Layout
2026-04-22 Mid of the routing
2026-04-23 Still layouting & mid of the Routing is going on
2026-04-23 Mid of the Routing almost done for Switch & then Still LED not started
2026-04-24 left side Layout of the Keyboard is done
    Partial side of the right design is also Done
2026-04-26 Design almost done for routing some changes in the footprint
2026-04-26 PCB Footprint updated
2026-04-26 PCB Layout is almost done Cosmetic Chnages need to do
2026-04-26 audio jack 3d model added to the Layout
2026-04-27 3D Step File Generated & Added
2026-04-28 making some cutout
2026-04-28 USB Hub design updated
2026-04-29 USB Circuit deleted & Design is also compeleted in LAyout level
2026-04-29 Double check with corne is also schematic apart from esd diode reset is done
